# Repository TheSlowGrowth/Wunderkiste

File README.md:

# Wunderkiste

A portable music player for children

Wunderkiste is a portable music player for young children. It's designed to be very easy to use so that even a 2 year-old child can quickly understand how it works. The whole projects is entirely open source so that YOU can build and modify it easily.

- Music is selected by placing a card / tag / figurine / cuddly toy on the top surface of Wunderkiste.
- Speakers are integreated, but headphones can be used, too.
- The integrated battery lasts multiple days of heavy use and can simply be charged with a USB phone charger.
- Music is stored as `*.mp3` files on an SD card. Wunderkiste can hold a very large library of music.
- New music can easily be added without any special tools or software.
- The build uses mostly through-hole components and should be doable by anyone with basic knowledge of soldering and a handfull of tools.
- The firmware can be updated easily.

# Building and using Wunderkiste

We collected a lot of information in the [Wiki tab of this repository](https://github.com/TheSlowGrowth/Wunderkiste/wiki). Here are some links to get started:

- [Download the latest release](https://github.com/TheSlowGrowth/Wunderkiste/releases/latest)
- [View the user manual](https://github.com/TheSlowGrowth/Wunderkiste/wiki/3.-How-to-use) (Work in progress)
- [View the build guide](https://github.com/TheSlowGrowth/Wunderkiste/wiki/2.-How-to-build) (Work in progress)
- [Report issues and bugs](https://github.com/TheSlowGrowth/Wunderkiste/issues)
- [Any contribution to the project is highly appreciated!](https://github.com/TheSlowGrowth/Wunderkiste/wiki/5.-How-to-contribute-to-the-project)

# Project structure

This software repository is the place where we collect everything needed to build, use, improve and customize your Wunderkiste.

The repository contains
- The source code for the firmware in the `firmware` directory.
- The hardware design files for the printed circuit boards in the `hardware` directory.
- Documentation and guides in the `docs` directory.
- The sources for the [Wiki](https://github.com/TheSlowGrowth/Wunderkiste/wiki) in the `docs/wiki` directory. They are automatically copied to the project wiki when pull requests are merged.
- CI actions in the `.github` directory (automated tests, release artifacts generation, etc.)

In addition to that, the github page contains
- [The Wiki tab](https://github.com/TheSlowGrowth/Wunderkiste/wiki) where you'll find a lot of resources
- [The Releases tab](https://github.com/TheSlowGrowth/Wunderkiste/releases) where you'll find all releases and the corresponding firmware images and other documents.

# How to contribute

Wunderkiste is open to use and modify by everyone. When we work together on this project, we can truely make something unique and wonderful. Please don't be shy to help improve this project!

- If you find something that you feel needs an improvement, feel free to [open an issue on the issues tab](https://github.com/TheSlowGrowth/Wunderkiste/issues) and let us know.
- [Browse the issues tab](https://github.com/TheSlowGrowth/Wunderkiste/issues) to see what's to do and where help is needed.
- [Fork this repo and make some changes](https://guides.github.com/activities/forking/), then open a pull request. We'll review your changes and merge them into this repository.

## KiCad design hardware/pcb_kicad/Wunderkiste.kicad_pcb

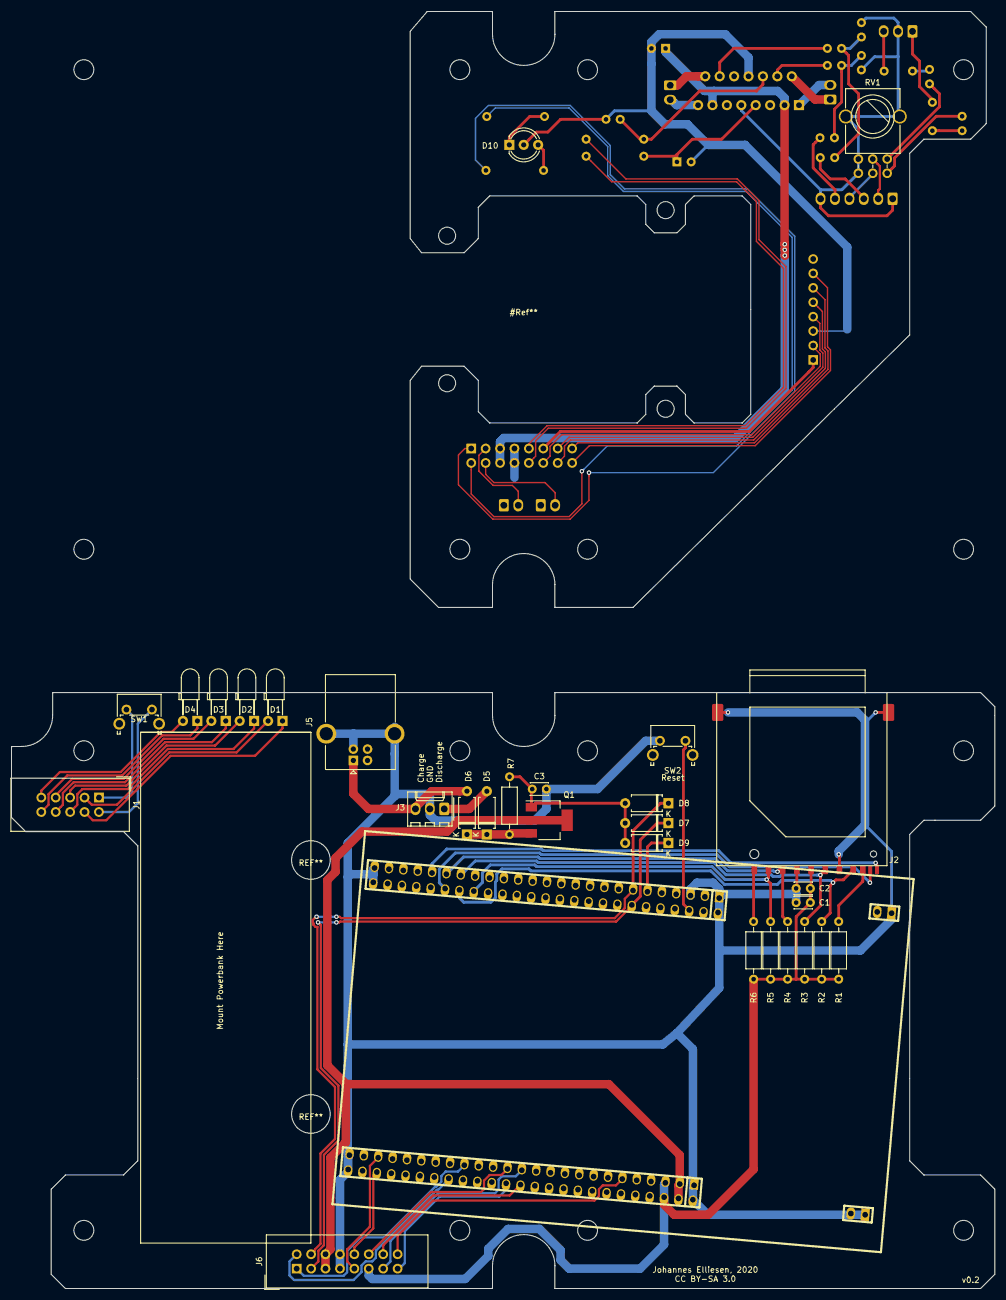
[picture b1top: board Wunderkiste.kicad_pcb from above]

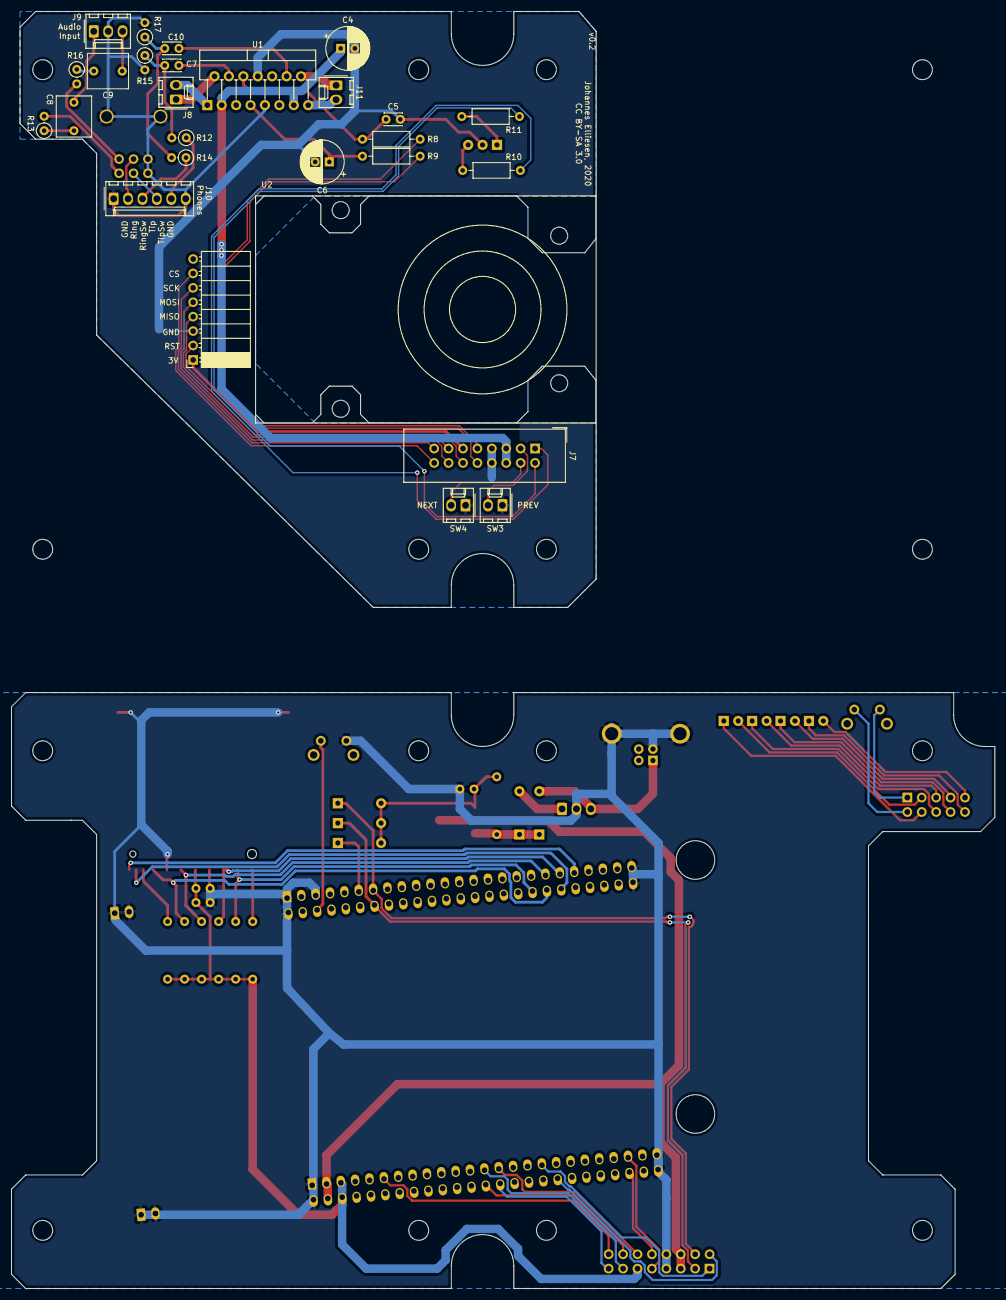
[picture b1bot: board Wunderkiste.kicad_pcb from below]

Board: 2 copper layers, 173.2 x 225.0 mm, 56 parts (26 on the bottom side), 71 nets.

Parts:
C1, C5: 1u; C_Disc_D3.0mm_W2.0mm_P2.50mm
C2, C3: 100n; C_Disc_D3.0mm_W2.0mm_P2.50mm
C4: 47u; CP_Radial_D7.5mm_P2.50mm
C6: 10u; CP_Radial_D7.5mm_P2.50mm
C7, C10: 220n; C_Disc_D3.0mm_W2.0mm_P2.50mm
C8, C9: 10u; C_Rect_L7.0mm_W6.0mm_P5.00mm
D1, D2, D3, D4: LED; LED_D3.0mm_Horizontal_O3.81mm_Z2.0mm
D5, D6, D7, D8, D9: 1N5819; D_A-405_P7.62mm_Horizontal
D10: LED_Dual_ACA; LED_D5.0mm-3
J1: Conn_01x10; IDC-Header_2x05_P2.54mm_Vertical
J2: SD_Card_Det; SD_Socket_SD-RSMT-2-10
J3: Powerbank; Molex_KK-254_AE-6410-03A_1x03_P2.54mm_Vertical
J4: STM32F4_Discovery; stm32f4_discovery
J5: USB_B; USB_B_OST_USB-B1HSxx_Horizontal
J6, J7: Conn_01x16; IDC-Header_2x08_P2.54mm_Vertical
J8: Spkr_L; Molex_KK-254_AE-6410-02A_1x02_P2.54mm_Vertical
J9: AudioIn; Molex_KK-254_AE-6410-03A_1x03_P2.54mm_Vertical
J10: Headphones; Molex_KK-254_AE-6410-06A_1x06_P2.54mm_Vertical
J11: Spkr_R; Molex_KK-254_AE-6410-02A_1x02_P2.54mm_Vertical
Q1: ISP75DP06LM; SOT-223
R1, R2, R3, R4, R5, R6, R7: 47k; R_Axial_DIN0207_L6.3mm_D2.5mm_P10.16mm_Horizontal
R8, R9: 10k; R_Axial_DIN0207_L6.3mm_D2.5mm_P10.16mm_Horizontal
R10: 470R; R_Axial_DIN0207_L6.3mm_D2.5mm_P10.16mm_Horizontal
R11: 2k2; R_Axial_DIN0207_L6.3mm_D2.5mm_P10.16mm_Horizontal
R12, R14, R15, R17: 10k; R_Axial_DIN0207_L6.3mm_D2.5mm_P2.54mm_Vertical
R13, R16: 0R; R_Axial_DIN0207_L6.3mm_D2.5mm_P2.54mm_Vertical
RV1: 50kA; 9mm_pot_dual
SW1: BatteryIndicator; SW_Tactile_SPST_Angled_PTS645Vx83-2LFS
SW2: Reset; SW_Tactile_SPST_Angled_PTS645Vx83-2LFS
SW3: PrevTrack; Molex_KK-254_AE-6410-02A_1x02_P2.54mm_Vertical
SW4: NextTrack; Molex_KK-254_AE-6410-02A_1x02_P2.54mm_Vertical
U1: TDA7266; TO-220-15_P2.54x2.54mm_StaggerOdd_Lead4.58mm_Vertical
U2: RFID_RC522_Board; RFID_RC_522_Board

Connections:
+3V0: C1.1, C2.1, J2.4, J4.95, J4.96, J6.11, J7.11, R1.1, R2.1, R3.1, R4.1, R5.1, R6.1, U2.1
+5V: C4.1, J4.97, J4.98, J6.5, J6.6, J7.5, J7.6, Q1.2, Q1.4, U1.3, U1.13
/AMP_MUTE: J4.56, J6.10
/AMP_MUTE_T: J7.10, R8.1
/AMP_STBY: J4.55, J6.9
/AMP_STBY_T: J7.9, R9.1
/POWER_HOLD: D9.1, J4.11
/RFID_CS: J4.89, J6.16
/RFID_CS_T: J7.16, U2.7
/RFID_MISO: J4.75, J6.13
/RFID_MISO_T: J7.13, U2.4
/RFID_MOSI: J4.76, J6.14
/RFID_MOSI_T: J7.14, U2.5
/RFID_RST: J4.73, J6.12
/RFID_RST_T: J7.12, U2.2
/RFID_SCK: J4.74, J6.15
/RFID_SCK_T: J7.15, U2.6
/Ring: J10.2, RV1.2
/RingNorm: J10.3, R14.1
/SD_AVAIL: J2.10, J4.40
/SD_CS: J2.1, J4.36, R5.2
/SD_MISO: J2.7, J4.38, R2.2
/SD_MOSI: J2.2, J4.39, R4.2
/SD_SCLK: J2.5, J4.37, R3.2
/SD_WRTPRT: J2.11, J4.41
/SW_NEXT: D8.1, J4.13, J6.4
/SW_NEXT_T: J7.4, SW4.2
/SW_PREV: D7.1, J4.14, J6.3
/SW_PREV_T: J7.3, SW3.2
/SW_RESET: J4.6, SW2.2
/TOP_LED_G: J4.67, J6.1
/TOP_LED_G_T: J7.1, R10.2
/TOP_LED_R: J4.66, J6.2
/TOP_LED_R_T: J7.2, R11.1
/Tip: J10.4, RV1.5
/TipNorm: J10.5, R12.1
GND: C1.2, C2.2, C3.2, C4.2, C5.2, C6.2, D10.2, J2.3, J2.6, J2.12, J3.2, J4.1, J4.2, J4.5, J4.49, J4.50, J4.51, J4.52, J4.99, J4.100, J5.4, J5.5, J6.7, J6.8, J7.7, J7.8, J9.2, J10.1, J10.6, R15.2, R17.2, RV1.1, RV1.4, RV1.7, SW2.1, SW3.1, SW4.1, U1.8, U1.9, U2.3
unnamed: C3.1, D7.2, D8.2, D9.2, Q1.1, R7.2
unnamed: C5.1, R8.2, U1.6
unnamed: C6.1, R9.2, U1.7
unnamed: C7.1, U1.4
unnamed: C7.2, R12.2, R15.1
unnamed: C8.1, R13.1
unnamed: C8.2, J9.1
unnamed: C9.1, J9.3
unnamed: C9.2, R16.1
unnamed: C10.1, U1.12
unnamed: C10.2, R14.2, R17.1
unnamed: D1.1, J1.4
unnamed: D1.2, J1.3
unnamed: D2.1, J1.6
unnamed: D2.2, J1.5
unnamed: D3.1, J1.8
unnamed: D3.2, J1.7
unnamed: D4.1, J1.10
unnamed: D4.2, J1.9
unnamed: D5.1, D6.1, Q1.3, R7.1
unnamed: D5.2, J3.1
unnamed: D6.2, J3.3, J5.1
unnamed: D10.1, R11.2
unnamed: D10.3, R10.1
unnamed: J1.1, SW1.1
unnamed: J1.2, SW1.2
unnamed: J2.8, R1.2
unnamed: J2.9, R6.2
unnamed: J8.1, U1.2
unnamed: J8.2, U1.1
unnamed: J11.1, U1.14
unnamed: J11.2, U1.15
unnamed: R13.2, RV1.6
unnamed: R16.2, RV1.3

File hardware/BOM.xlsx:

PCB designators | Description | Value | Count | reichelt.de part number | reichelt.de price per unit | reichelt.de total price | mouser.com part number | Notes
C1 C5 | Ceramic or Wima, >5V, 2.54mm pin pitch | 1u | 2 | Z5U-5 1,0µ | 0.27 | 0.54
C7 C10 |  | 220n | 2 | Z5U-2,5 220N | 0.10299999999999999 | 0.20599999999999999
C2 C3 |  | 100n | 2 | Z5U-2,5 100N | 6.2E-2 | 0.124
C4 |  | 47u | 1 | RAD FC 47/25 | 0.123 | 0.123
C6 C8 C9 | Bipolar Electrolytic Capacitor | 10u Bipolar | 3 | SU-A 10U 50 | 0.21 | 0.63
D1 D2 D3 D4 |  | LED | 4 | LED 3MM 2MA GN | 0.12 | 0.48
D10 | Frontpanel LED R/G | 5mm, 3pin Common Anode, Red/Green | 1 | EVL 339-1SURSYGW | 0.2 | 0.2
D5 D6 D7 D8 D9 |  | 1N5819 | 5 | 1N 5819 | 0.06 | 0.3
J1 | Powerbank LED/Button cable | IDC Shrouded pinheader 2x5 | 1 | WSL 10G | 0.1 | 0.1
 |  | IDC Socker 2x5 | 1 | PFL 10 | 0.1 | 0.1
J10 | Headphones socket cable connector | Molex KK 6pin Pinheader | 1 | PSS 254/6G | 0.09 | 0.09
 |  | Molex KK 6pin Housing | 1 | PSK 254/6W | 7.0000000000000007E-2 | 7.0000000000000007E-2
J2 | SD Card Slot | SD-RSMT-2-MQ | 1 | 3M SDRSMT2MQ | 2.1 | 2.1
J4 |  | 2x25 sockets | 2 | BL 2X25G8 2,54 | 0.62 | 1.24 | 200-SSW12501TD
J5 | USB charging connector | USB B socket Through Hole | 1 | RND 205-00858 | 0.25 | 0.25
J6 J7 | PCB interconnect cable | IDC Shrouded pinheader 2x8 | 2 | WSL 16G | 0.14000000000000001 | 0.28000000000000003
 |  | IDC Socker 2x8 | 2 | PFL 16 | 0.18 | 0.36
J3 J9 | AudioIn & PowerBank Connectors | Molex KK 3pin Pinheader | 2 | PSS 254/3G | 5.0999999999999997E-2 | 0.10199999999999999
 |  | Molex KK 3pin Housing | 2 | PSK 254/3W | 0.02 | 0.04
Q1 | P Channel Mosfet | BSP170P | 1 | BSP170P | 0.45 | 0.45
R10 |  | 470R | 1 | METALL 470 | 8.2000000000000003E-2 | 8.2000000000000003E-2
R11 |  | 2k2 | 1 | METALL 2,20K | 8.2000000000000003E-2 | 8.2000000000000003E-2
R8 R9 R12 R14 R15 R17 |  | 10k | 6 | METALL 10,0K | 8.2000000000000003E-2 | 0.49199999999999999 |  | get 10 for the same price due to the quantity discount
R13 R16 |  | 0R | 2 |  |  | 0 |  | use wire bridges for full volume, attenuate volume with up to 50k resistors
R1 R2 R3 R4 R5 R6 R7 |  | 47k | 7 | METALL 47,0K | 8.2000000000000003E-2 | 0.57400000000000007
RV1 | Dual Gang 9mm Potentiometer | 50kA or 47kA, log, RK09 footprint, Alps/Alpha/… | 1 |  |  | 0
SW1 SW 2 | BatteryIndicator & Reset buttons | horizontal push button | 2 | TASTER 3305 | 0.21 | 0.42
SW3 SW4 J8 J11 | Prev Bttn, Next Bttn, Speaker Connectors | Molex KK 2pin Pinheader | 4 | PSS 254/2G | 0.03 | 0.12
 |  | Molex KK 2pin Housing | 4 | PSK 254/2W | 0.02 | 0.08
U1 | Speaker Amplifier | TDA7266 | 1 | TDA 7266 | 1.7 | 1.7
U2 | RFID Reader board | RFID_RC522_Board | 1 | DEBO RFID RC522 | 10.37 | 10.37 |  | better get this off ebay for MUCH cheaper
 |  | Crimp Pins Molex, pack of 20 | 2 | PSK-KONTAKTE | 0.28999999999999998 | 0.57999999999999996
 | Volume Knob Cap | Mounts on RV1 | 1 | KNOPF 17-6 AL | 2.17 | 2.17
 | STM32F407 Discovery board | STM32F407DISCOVERY | 1 | STM32 F407GDISC1 | 29.75 | 29.75 |  | Attention: Buy version number MB997D for MUCH simpler drag&drop programming
 | Frontpanel Pushbuttons |  | 2 | IS R3S RT | 5.8 | 11.6 |  | doesn't have to be that expensive, any momentary pushbutton will work just fine
 | LED frontpanel socket | 5mm | 1 | EBF A-5 S | 0.99 | 0.99
 | Enclosure (screws included) | Hammond 1591XXEBK | 1 | 1591XXEBK | 9.35 | 9.35
 | Headphone Jack | Stereo, switched, 3.5mm | 1 | LUM 1503-09 | 1.1499999999999999 | 1.1499999999999999 | 490-SJ1-3535 | the thread is a little short on this part but it's just enough
 | Speakers | Visaton BF 37 | 2 | VIS 2260 | 11.4 | 22.8
 | Powerbank | Intenso A5200 | 1 | INTENSO 7322425 | 10.36 | 10.36
 | SD Card |  | 1 | INTENSO SDHC16G | 3.49 | 3.49
 | Screws for mounting the speakers & RFID | M2.5 countersunk, 10mm length max | 1 | SSK M2,5X10-200 | 2.7 | 2.7 |  | pack of 200
 | Nuts for mounting the speakers & RFID | M2.5 | 1 | SK M2,5-100 | 1.85 | 1.85 |  | pack of 100
 | Self tapping screws | # 4 x 1/4 |  |  |  | 0 |  | for mounting PCB inside the Hammond enclosure; M2.5 screws might work as well
 | RFID cards, tags, stickers | Mifare Classik 1K compatible |  |  |  | 0
 | Speaker grille (?) | any metal mesh material | 1 | VIS SG 8210 | 8.9499999999999993 | 8.9499999999999993 |  | Any metal mesh will do. Cheap alternative: Frying Pan Grease Splash Guard
 | Cable, blue, 10m |  | 1 | LITZE BL | 0.78 | 0.78
 | Cable, black, 10m |  | 1 | LITZE SW | 0.78 | 0.78
 | Cable, red, 10m |  | 1 | LITZE RT | 0.76 | 0.76
 | IDC flat cable |  | 1 | AWG 28-20F 3M | 5.25 | 5.25 |  | way too long. Maybe you have some leftover IDC cable from another project?
 | Rubber feet with adhesive |  | 1 | RND 455-00518 | 0.82 | 0.82 |  | pack of 55… some felt furniture feet will also work.
 | PCB Material for the speaker covers |  | 1 | EP2CU 160X100 | 2.0499999999999998 | 2.0499999999999998
 |  |  |  |  | Total price: | 110.45499999999998

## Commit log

2020-12-29 Added initial firmware source files
2020-12-29 Added Visual Studio Code integration files
2020-12-29 Added hardware designs v0.1
2020-12-29 small cleanups, renamed variables
2020-12-29 Player now waits until the buffer has cleared before jumping to the next file. Fixes issue #1
2020-12-29 Fixed launch.json to use "${env:HOME}" instead of "~" in file paths
2020-12-29 Added button debouncing; added UI event queue; improved previous button behaviour
    Fixes #5
2020-12-29 Fixed strncpy possibly skipping the terminating zero
2020-12-29 formatting fixes to remove warnings
2020-12-29 Added a simple CI test build for pull requests
    Fixes #9
2020-12-29 removed duplicate STM32 peripheral library
2020-12-29 Added GPLv3 licenses to various source files; Added LICENSE file
2020-12-29 Test action now archives the generated hex file
2020-12-29 make all also generates the firmware *.bin file
2020-12-29 Renamed existing test build action
2020-12-29 Added an action to generate release assets
2020-12-30 Added an action to generate GitHub releases for v* tags
2020-12-30 Renamed development test build action; action is now run more often
2020-12-30 Included the current contents of the wiki; Added action that copies "docs/wiki" to the GitHub wiki on each push on "master"
2021-01-01 Added a brief user manual
2021-01-01 Improved the readme
2021-01-01 Fixed image links in documentation and readme
2021-01-01 Fixed Wiki update action so that images are also copied
2021-01-01 Added firmware update instructions to the user manual
2021-01-02 Reallocated custom kicad symbols into a local symbol library
2021-01-02 Fixed DRC errors in the pcb file
2021-01-02 Added KiBot configuration file
2021-01-02 Fixed ERC errors
2021-01-02 Renamed the software check action
2021-01-02 Added Hardware Checks badge
2021-01-02 Added a hardware check action
2021-01-02 Add Generation of hardware design files to release action
2021-01-02 Hardware check action now triggers on changes to KiBot config file
2021-01-02 Firmware checks now only run when firmware files are changed
2021-01-02 KiBot now generates the drill template from the Dwgs.User layer
2021-01-02 Improved drill template on the Dwgs.User layer
2021-01-09 Fixed Mosfet that had the wrong part number
2021-01-10 Added BOM
2021-02-07 Added googletest submodule
2021-02-07 Added googletest Makefile; added VsCode launch configurations; added a dummy test
2021-02-07 Moved .vscode directory to the repository root; small adjustments
2021-02-07 Removed the dummy test
2021-02-07 Checks are now also triggered when github action files are changed
2021-02-07 Added googletests to the github actions CI
2021-02-08 Switched firmware to C++17
2021-02-08 Fixed vscode launch file pointing to the wrong binary path
2021-02-08 Added _clang-format
2021-03-20 Added "dependsOrder": "sequence" to clean-build tasks
2021-03-20 FatFs: updated from R0.11 to R0.14a; replaced diskio implementation
2021-03-20 Rewrote the firmware in C++
2021-03-20 Various improvements for compiling and debugging under Windows
2021-03-20 Added return value to File::close() to catch write errors when flushing the buffers
2021-03-21 Fixed LED driver having an accidental Pullup enabled
2021-03-22 Improved reliability of SD card driver
2021-03-22 Updated release workflow to remove /refs/tags/ from the release name, so that asset downloads won't fail
2021-03-22 Improved firmware update instructions for older STM32F4 Discovery boards
2021-03-22 Removed old files from the initial C application; adjusted new application files where old headers were still included by accident
2021-03-22 Added missing GPL header
2021-03-22 Removed unused STM source files for STM32F0xx, STM32F10x, STM32F37x and DSP_Lib
2021-03-22 Added info to the "how to setup for development" wiki page
2021-03-22 Renamed include guard in DAC.h
2021-03-22 Added contribution guide and code style documentation
2021-03-22 Moved googletest submodule to lib/
2021-03-22 Added format check action
2021-03-22 Applied clang-format to all files
2021-03-23 Fixed include paths in .vscode/c_cpp_properties.json
2021-03-23 Fixed typos in the wiki
2021-03-23 Increased maximum file path length
2021-04-09 Small fixes in BOM.xlsx
2021-04-09 BOM.xlsx is now added to the release artifacts
2021-04-09 Added the written build guide
    Fixes #4
2021-04-10 Fixed typos in the wiki; small improvements
2021-07-25 fix: correctly display error code when SD cannot be mounted
2021-07-29 fix: improve mounting/unmounting of SD card
2021-07-29 add CHANGELOG.md
2021-07-29 fix release action
2021-07-29 fix hardwareChecks action

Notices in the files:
hardware/pcb_kicad/Wunderkiste.kicad_pcb:
CC BY-SA 3.0
